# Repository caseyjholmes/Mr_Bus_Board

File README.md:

# Mr_Bus_Board
8 module mini bus board for small eurorack cases by Holmes Modular 5/6/23

Here is some 3D printable cases to fit the bus boards 

https://github.com/caseyjholmes/pyramidSkiff

https://www.thingiverse.com/thing:6074179

https://www.thingiverse.com/thing:6085424

7/9/23 - board was updated. Fixed a silkscreen issue (no biggie), added part numbers to the BOM for the leds and updated the resistors to help equalize the LED brightness. Little better now.

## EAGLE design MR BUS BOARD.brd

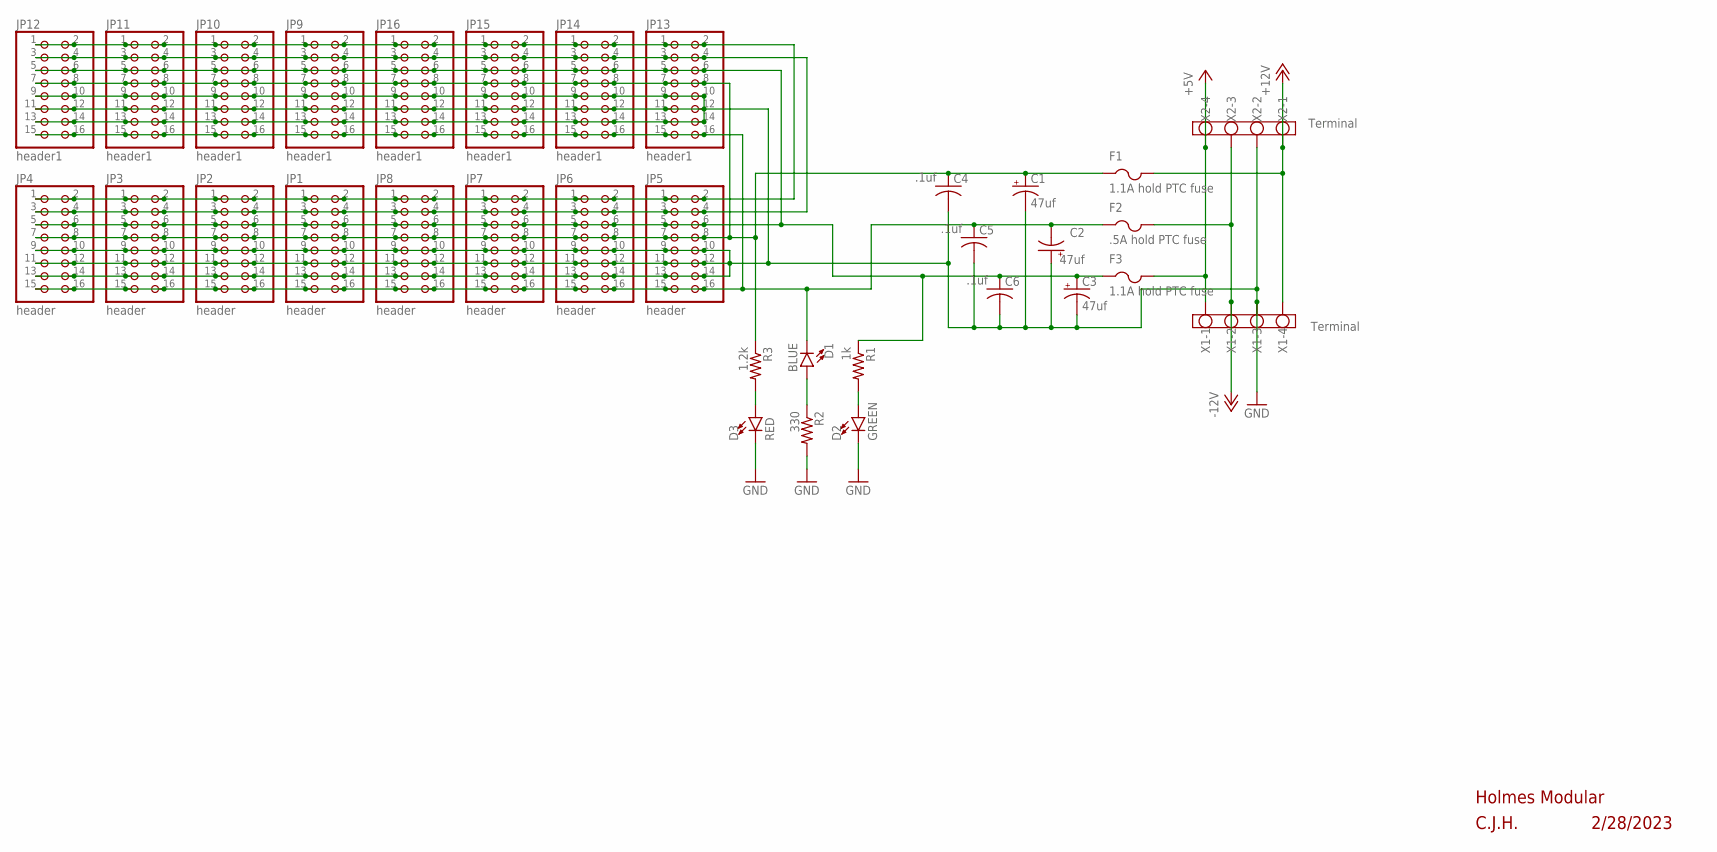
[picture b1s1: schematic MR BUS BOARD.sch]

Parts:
C1, C2, C3: 47uf; PANASONIC_D
C4, C5, C6: .1uf; C0805K
D1: BLUE; LED-0603
D2: GREEN; LED-0603
D3: RED; LED-0603
F1, F3: 1.1A hold PTC fuse; 1812
F2: .5A hold PTC fuse; 1812
JP1, JP2, JP3, JP4, JP5, JP6, JP7, JP8: header; 2X08_SMT
JP9, JP10, JP11, JP12, JP13, JP14, JP15, JP16: header1; 2X08
R1: 1k; R0805
R2: 330; R0805
R3: 1.2k; R0805
X1, X2: Terminal; W237-4

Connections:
+5V: F3.2, X1.1, X2.4
+12V: F1.2, X1.4, X2.1
-12V: F2.2, X1.2, X2.3
GND: C1.-, C2.+, C3.-, C4.2, C5.2, C6.2, D2.C, D3.C, JP1.9, JP1.10, JP1.11, JP1.12, JP1.13, JP1.14, JP2.9, JP2.10, JP2.11, JP2.12, JP2.13, JP2.14, JP3.9, JP3.10, JP3.11, JP3.12, JP3.13, JP3.14, JP4.9, JP4.10, JP4.11, JP4.12, JP4.13, JP4.14, JP5.9, JP5.10, JP5.11, JP5.12, JP5.13, JP5.14, JP6.9, JP6.10, JP6.11, JP6.12, JP6.13, JP6.14, JP7.9, JP7.10, JP7.11, JP7.12, JP7.13, JP7.14, JP8.9, JP8.10, JP8.11, JP8.12, JP8.13, JP8.14, JP9.9, JP9.10, JP9.11, JP9.12, JP9.13, JP9.14, JP10.9, JP10.10, JP10.11, JP10.12, JP10.13, JP10.14, JP11.9, JP11.10, JP11.11, JP11.12, JP11.13, JP11.14, JP12.9, JP12.10, JP12.11, JP12.12, JP12.13, JP12.14, JP13.9, JP13.10, JP13.11, JP13.12, JP13.13, JP13.14, JP14.9, JP14.10, JP14.11, JP14.12, JP14.13, JP14.14, JP15.9, JP15.10, JP15.11, JP15.12, JP15.13, JP15.14, JP16.9, JP16.10, JP16.11, JP16.12, JP16.13, JP16.14, R2.2, X1.3, X2.2
unnamed: JP1.1, JP1.2, JP2.1, JP2.2, JP3.1, JP3.2, JP4.1, JP4.2, JP5.1, JP5.2, JP6.1, JP6.2, JP7.1, JP7.2, JP8.1, JP8.2, JP9.1, JP9.2, JP10.1, JP10.2, JP11.1, JP11.2, JP12.1, JP12.2, JP13.1, JP13.2, JP14.1, JP14.2, JP15.1, JP15.2, JP16.1, JP16.2
unnamed: C2.-, C5.1, D1.C, F2.1, JP1.15, JP1.16, JP2.15, JP2.16, JP3.15, JP3.16, JP4.15, JP4.16, JP5.15, JP5.16, JP6.15, JP6.16, JP7.15, JP7.16, JP8.15, JP8.16, JP9.15, JP9.16, JP10.15, JP10.16, JP11.15, JP11.16, JP12.15, JP12.16, JP13.15, JP13.16, JP14.15, JP14.16, JP15.15, JP15.16, JP16.15, JP16.16
unnamed: D3.A, R3.2
unnamed: D1.A, R2.1
unnamed: C1.+, C4.1, F1.1, JP1.7, JP1.8, JP2.7, JP2.8, JP3.7, JP3.8, JP4.7, JP4.8, JP5.7, JP5.8, JP6.7, JP6.8, JP7.7, JP7.8, JP8.7, JP8.8, JP9.7, JP9.8, JP10.7, JP10.8, JP11.7, JP11.8, JP12.7, JP12.8, JP13.7, JP13.8, JP14.7, JP14.8, JP15.7, JP15.8, JP16.7, JP16.8, R3.1
unnamed: D2.A, R1.2
unnamed: JP1.3, JP1.4, JP2.3, JP2.4, JP3.3, JP3.4, JP4.3, JP4.4, JP5.3, JP5.4, JP6.3, JP6.4, JP7.3, JP7.4, JP8.3, JP8.4, JP9.3, JP9.4, JP10.3, JP10.4, JP11.3, JP11.4, JP12.3, JP12.4, JP13.3, JP13.4, JP14.3, JP14.4, JP15.3, JP15.4, JP16.3, JP16.4
unnamed: C3.+, C6.1, F3.1, JP1.5, JP1.6, JP2.5, JP2.6, JP3.5, JP3.6, JP4.5, JP4.6, JP5.5, JP5.6, JP6.5, JP6.6, JP7.5, JP7.6, JP8.5, JP8.6, JP9.5, JP9.6, JP10.5, JP10.6, JP11.5, JP11.6, JP12.5, JP12.6, JP13.5, JP13.6, JP14.5, JP14.6, JP15.5, JP15.6, JP16.5, JP16.6, R1.1

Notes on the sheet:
Holmes Modular
C.J.H.
2/28/2023

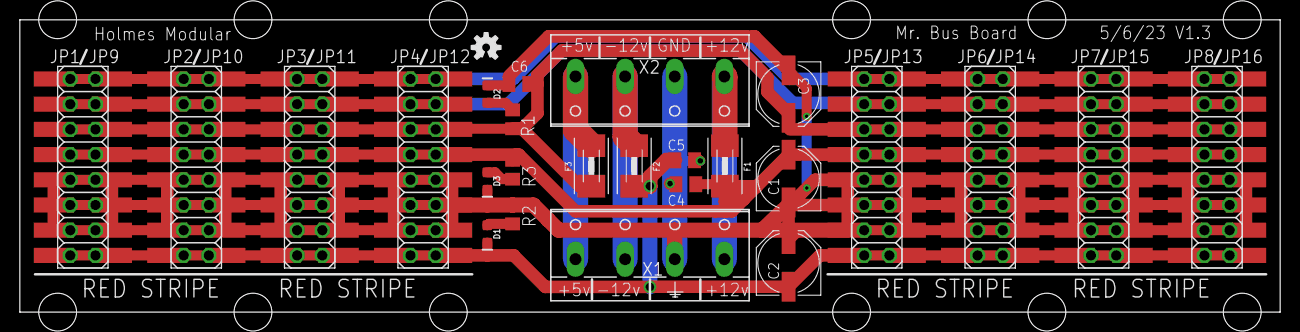
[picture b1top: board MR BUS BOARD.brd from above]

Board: 2 copper layers, 127.0 x 29.5 mm, 34 parts (0 on the bottom side), 12 nets.

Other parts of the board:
U$2: OSHW-LOGO-S

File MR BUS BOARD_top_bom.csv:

Comment,Designator,Footprint,LCSC Part #
.1uf,C4 C5 C6,C0805K,
.5A hold PTC fuse,F2,1812,
1.1A hold PTC fuse,F3,1812,
1.1A hold PTC fuse ,F1,1812,
1.2k,R3,R0805,
1k,R1,R0805,
47uf,C1 C2 C3,PANASONIC_D,
330,R2,R0805,
BLUE,D1,LED-0603,
GREEN,D2,LED-0603,
RED,D3,LED-0603,
header,JP1 JP2 JP3 JP4 JP5 JP6 JP7 JP8,2X08_SMT,

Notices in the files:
parts and their libraries:
SparkFun-Aesthetics: Licensing: Creative Commons ShareAlike 4.0 International - https://creativecommons.org/licenses/by-sa/4.0
